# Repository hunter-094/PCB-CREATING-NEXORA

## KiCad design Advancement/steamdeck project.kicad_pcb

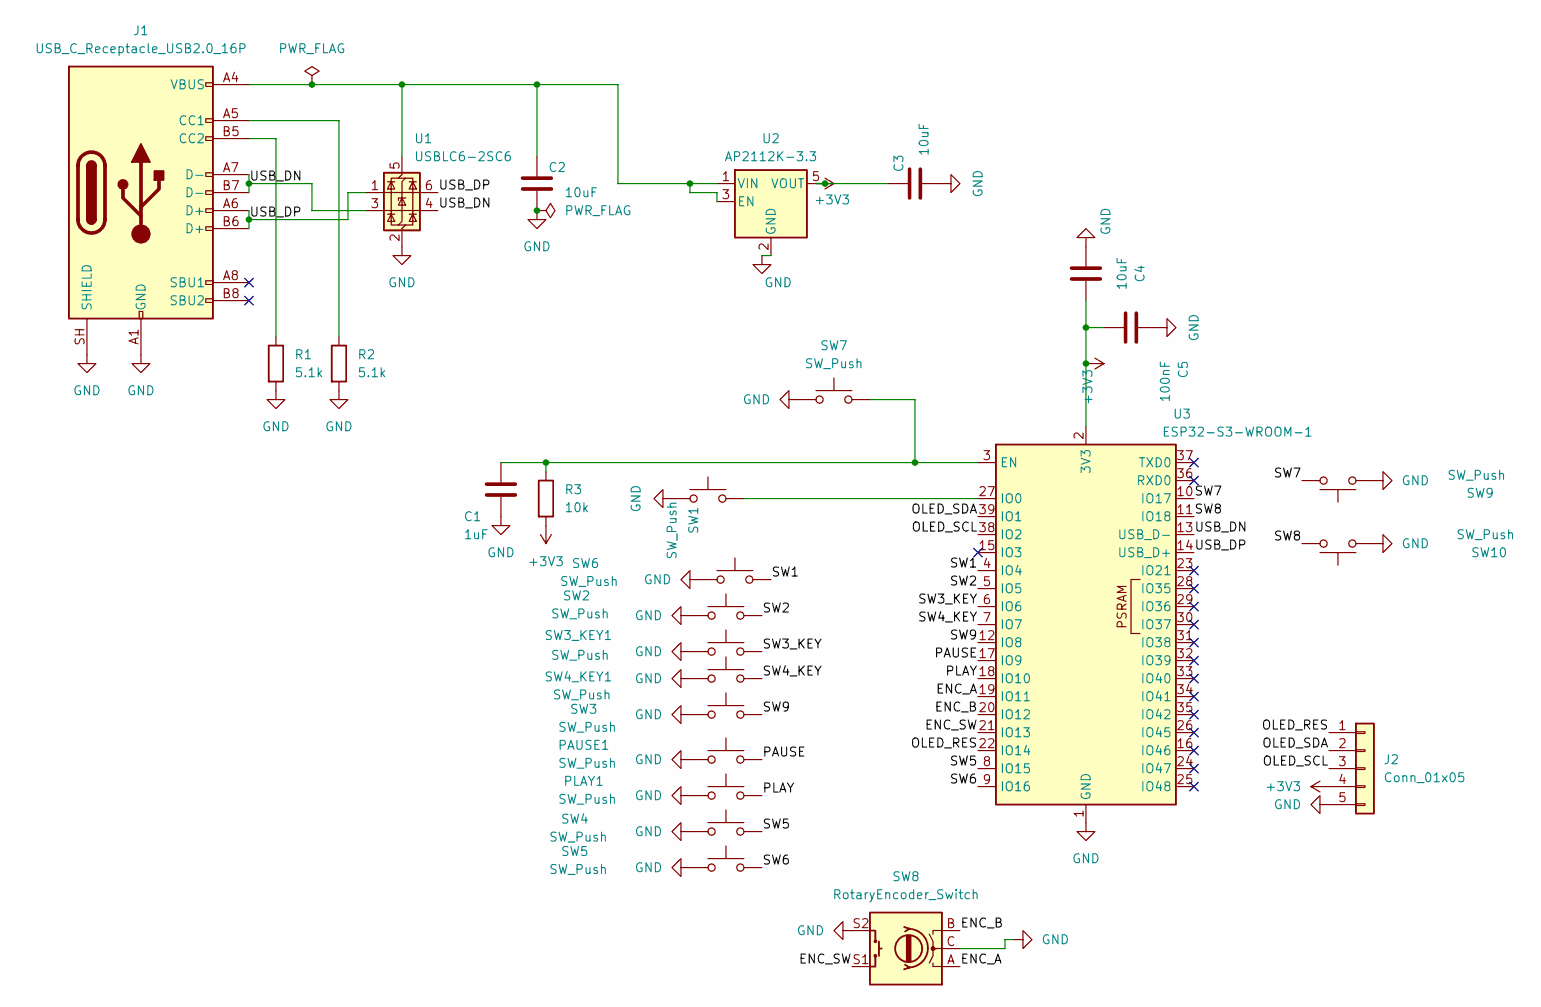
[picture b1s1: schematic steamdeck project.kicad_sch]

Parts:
C1: 1uF; C_0603_1608Metric
C2, C3, C4: 10uF; C_0805_2012Metric
C5: 100nF; C_0603_1608Metric
J1: USB_C_Receptacle_USB2.0_16P; USB_C_Receptacle_HRO_TYPE-C-31-M-12
J2: Conn_01x05; PinSocket_1x05_P2.54mm_Vertical
PAUSE1: SW_Push; SW_Cherry_MX_1.00u_PCB
PLAY1: SW_Push; SW_Cherry_MX_1.00u_PCB
R1, R2: 5.1k; R_0603_1608Metric
R3: 10k; R_0603_1608Metric
SW1, SW7: SW_Push; SW_SPST_PTS645Sx43SMTR92
SW2, SW3, SW3_KEY1, SW4, SW4_KEY1, SW5, SW6, SW9, SW10: SW_Push; SW_Cherry_MX_1.00u_PCB
SW8: RotaryEncoder_Switch; RotaryEncoder_Alps_EC11E-Switch_Vertical_H20mm
U1: USBLC6-2SC6; SOT-23-6
U2: AP2112K-3.3; SOT-23-5
U3: ESP32-S3-WROOM-1

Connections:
+3V3: C3.1, C4.2, C5.1, J2.4, R3.2, U2.5 (VOUT), U3.2 (3V3)
/ENC_A: SW8.A, U3.19 (IO11)
/ENC_B: SW8.B, U3.20 (IO12)
/ENC_SW: SW8.S1, U3.21 (IO13)
/OLED_RES: J2.1, U3.22 (IO14)
/OLED_SCL: J2.3, U3.38 (IO2)
/OLED_SDA: J2.2, U3.39 (IO1)
/PAUSE: PAUSE1.2, U3.17 (IO9)
/PLAY: PLAY1.2, U3.18 (IO10)
/SW1: SW6.2, U3.4 (IO4)
/SW2: SW2.2, U3.5 (IO5)
/SW3_KEY: SW3_KEY1.2, U3.6 (IO6)
/SW4_KEY: SW4_KEY1.2, U3.7 (IO7)
/SW5: SW4.2, U3.8 (IO15)
/SW6: SW5.2, U3.9 (IO16)
/SW7: SW9.2, U3.10 (IO17)
/SW8: SW10.2, U3.11 (IO18)
/SW9: SW3.2, U3.12 (IO8)
/USB_DN: J1.A7 (D-), J1.B7 (D-), U1.3 (I/O2), U1.4 (I/O2), U3.13 (USB_D-)
/USB_DP: J1.A6 (D+), J1.B6 (D+), U1.1 (I/O1), U1.6 (I/O1), U3.14 (USB_D+)
GND: C1.2, C2.2, C3.2, C4.1, C5.2, J1.A1 (GND), J1.A12 (GND), J1.B1 (GND), J1.B12 (GND), J1.SH (SHIELD), J2.5, PAUSE1.1, PLAY1.1, R1.2, R2.2, SW1.1, SW2.1, SW3.1, SW3_KEY1.1, SW4.1, SW4_KEY1.1, SW5.1, SW6.1, SW7.1, SW8.C, SW8.S2, SW9.1, SW10.1, U1.2 (GND), U2.2 (GND), U3.1 (GND), U3.40 (GND), U3.41 (GND)
unnamed: J1.A5 (CC1), R2.1
unnamed: J1.B5 (CC2), R1.1
unnamed: C2.1, J1.A4 (VBUS), J1.A9 (VBUS), J1.B4 (VBUS), J1.B9 (VBUS), U1.5 (VBUS), U2.1 (VIN), U2.3 (EN)
unnamed: C1.1, R3.1, SW7.2, U3.3 (EN)
unnamed: SW1.2, U3.27 (IO0)

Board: 2 copper layers, 27 parts (0 on the bottom side), 26 nets, no tracks yet.

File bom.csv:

Référence,Valeur,Quantité,Empreinte,Description,Lien
U3,ESP32-S3-WROOM-1-N16R8,1,RF_Module:ESP32-S3-WROOM-1,"Module ESP32-S3, 16 Mo flash, 8 Mo PSRAM (PCB final)",https://www.mouser.fr/c/?q=ESP32-S3-WROOM-1-N16R8
U2,AP2112K-3.3,1,Package_TO_SOT_SMD:SOT-23-5,"Régulateur 3,3 V",https://www.lcsc.com/search?q=AP2112K-3.3
U1,USBLC6-2SC6,1,Package_TO_SOT_SMD:SOT-23-6,Protection ESD USB,https://www.lcsc.com/search?q=USBLC6-2SC6
J1,USB-C 16 broches,1,Connector_USB:USB_C_Receptacle_HRO_TYPE-C-31-M-12,Connecteur USB-C CMS,https://www.lcsc.com/search?q=USB-C+16pin
J2,Header femelle 1x05,1,Connector_PinSocket_2.54mm:PinSocket_1x05_P2.54mm_Vertical,Connecteur de l'écran OLED,https://www.amazon.fr/s?k=barrette+femelle+2.54mm
"R1, R2","5,1 kΩ",2,Resistor_SMD:R_0603_1608Metric,Résistances CC de l'USB-C,https://www.lcsc.com/search?q=5.1k+0603
R3,10 kΩ,1,Resistor_SMD:R_0603_1608Metric,Pull-up du reset (EN),https://www.lcsc.com/search?q=10k+0603
C1,1 µF,1,Capacitor_SMD:C_0603_1608Metric,Condensateur du reset,https://www.lcsc.com/search?q=1uF+0603
"C2, C3, C4",10 µF,3,Capacitor_SMD:C_0805_2012Metric,Découplage alimentation,https://www.lcsc.com/search?q=10uF+0805
C5,100 nF,1,Capacitor_SMD:C_0603_1608Metric,Découplage du module,https://www.lcsc.com/search?q=100nF+0603
"SW1, SW7",Bouton tact CMS,2,Button_Switch_SMD:SW_SPST_PTS645Sx43SMTR92,Boutons Boot et Reset,https://www.lcsc.com/search?q=SMD+tact+switch
"SW2-SW6, SW9, SW10, SW3_KEY1, SW4_KEY1, PAUSE1, PLAY1",Switch MX 3 broches,11,Button_Switch_Keyboard:SW_Cherry_MX_1.00u_PCB,9 raccourcis + Pause + Play,https://www.amazon.fr/s?k=switch+cherry+MX+mecanique
SW8,Encodeur EC11 avec bouton,1,Rotary_Encoder:RotaryEncoder_Alps_EC11E-Switch_Vertical_H20mm,Volume et mute,https://www.amazon.fr/s?k=encodeur+rotatif+EC11
-,"Écran OLED 2,42"" SSD1309 128x64 I2C",1,-,"Module écran (5 broches : RES, SDA, SCL, VCC, GND)",https://www.amazon.fr/s?k=ecran+OLED+2.42+pouces+SSD1309+128x64
-,Keycaps MX,11,-,Capuchons des touches,https://www.amazon.fr/s?k=keycaps+MX
-,Knob 15 à 20 mm,1,-,Bouton de l'encodeur,https://www.amazon.fr/s?k=bouton+encodeur+rotatif+15mm
-,Inserts filetés M3,4,-,Fixation dans le boîtier,https://www.amazon.fr/s?k=inserts+filetes+M3+impression+3D
-,Vis M3 6 à 8 mm,4,-,Fixation du PCB,https://www.amazon.fr/s?k=vis+M3+8mm
-,Boîtier impression 3D (PETG ou PLA),1,-,Boîtier 150 x 80 mm,-
-,Câble USB-C avec données,1,-,Alimentation et connexion au PC,-
PROTOTYPE,Carte ESP32-S3-DevKitC-1 N16R8,1,-,Pour tester avant le PCB,https://www.amazon.fr/s?k=ESP32-S3-DevKitC-1+N16R8
PROTOTYPE,Breadboard,1,-,Câblage du prototype,https://www.amazon.fr/s?k=breadboard+830+points
PROTOTYPE,Fils Dupont,1,-,Câblage du prototype,https://www.amazon.fr/s?k=fils+dupont+kit

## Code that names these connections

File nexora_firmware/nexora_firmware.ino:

/*
  NEXORA - firmware ESP32-S3 (WROOM-1 N16R8)
  ------------------------------------------
  - 9 touches de raccourci  -> envoient F13 a F21 (a associer a des actions
    sur le PC avec PowerToys, AutoHotkey, Steam, OBS, etc.)
  - Touches PAUSE / PLAY    -> controle media (lecture/pause, piste suivante)
  - Encodeur rotatif        -> volume +/- ; clic = mute
  - Ecran OLED SSD1309 128x64 (I2C) -> affiche la derniere action et le volume

  Branchement (voir le schema KiCad) :
    Touches : IO4, IO5, IO6, IO7, IO15, IO16, IO17, IO18, IO8
    PAUSE IO9, PLAY IO10
    Encodeur : A IO11, B IO12, bouton IO13
    OLED : SDA IO1, SCL IO2, RES IO14

  Reglages dans l'IDE Arduino (core "esp32" d'Espressif) :
    Carte       : ESP32S3 Dev Module
    USB Mode    : USB-OTG (TinyUSB)
    PSRAM       : OPI PSRAM
    Flash Size  : 16MB
  Bibliotheque a installer : U8g2 (par olikraus)

  Pour flasher : brancher le port USB natif en maintenant le bouton BOOT,
  appuyer sur RESET, puis relacher BOOT.
*/

#include <Arduino.h>
#include <Wire.h>
#include <U8g2lib.h>
#include "USB.h"
#include "USBHIDKeyboard.h"
#include "USBHIDConsumerControl.h"

// ---------- Broches ----------
#define PIN_OLED_SDA 1
#define PIN_OLED_SCL 2
#define PIN_OLED_RES 14

#define PIN_ENC_A  11
#define PIN_ENC_B  12
#define PIN_ENC_SW 13

// ---------- Objets ----------
USBHIDKeyboard        Keyboard;
USBHIDConsumerControl Consumer;
U8G2_SSD1309_128X64_NONAME0_F_HW_I2C u8g2(U8G2_R0, PIN_OLED_RES);

// ---------- Description des touches ----------
enum ActionType { ACT_KEY, ACT_MEDIA };

struct Btn {
  uint8_t       pin;
  const char*   name;     // texte affiche sur l'ecran
  ActionType    type;
  uint16_t      code;     // code HID (clavier) ou code media
  bool          pressed;
  unsigned long lastChange;
};

// Codes HID bruts : F13 = 0x68 ... F21 = 0x70
// Pour changer une action, modifie simplement la ligne correspondante.
Btn buttons[] = {
  {4,  "Touche 1", ACT_KEY,   0x68, false, 0},  // F13
  {5,  "Touche 2", ACT_KEY,   0x69, false, 0},  // F14
  {6,  "Touche 3", ACT_KEY,   0x6A, false, 0},  // F15
  {7,  "Touche 4", ACT_KEY,   0x6B, false, 0},  // F16
  {15, "Touche 5", ACT_KEY,   0x6C, false, 0},  // F17
  {16, "Touche 6", ACT_KEY,   0x6D, false, 0},  // F18
  {17, "Touche 7", ACT_KEY,   0x6E, false, 0},  // F19
  {18, "Touche 8", ACT_KEY,   0x6F, false, 0},  // F20
  {8,  "Touche 9", ACT_KEY,   0x70, false, 0},  // F21
  {9,  "Lecture/Pause", ACT_MEDIA, CONSUMER_CONTROL_PLAY_PAUSE, false, 0},
  {10, "Piste suivante", ACT_MEDIA, CONSUMER_CONTROL_SCAN_NEXT,  false, 0},
};
const uint8_t NB_BTN = sizeof(buttons) / sizeof(buttons[0]);
const unsigned long DEBOUNCE_MS = 20;

// ---------- Encodeur ----------
volatile int16_t encAcc = 0;
volatile uint8_t encState = 0;

void IRAM_ATTR encISR() {
  static const int8_t table[16] = {0, -1, 1, 0, 1, 0, 0, -1, -1, 0, 0, 1, 0, 1, -1, 0};
  encState = ((encState << 2) | (digitalRead(PIN_ENC_A) << 1) | digitalRead(PIN_ENC_B)) & 0x0F;
  encAcc += table[encState];
}

bool encPressed = false;
unsigned long encLastChange = 0;

// ---------- Affichage ----------
String lastAction = "NEXORA pret";
int    volumeLevel = 50;          // estimation locale, juste pour l'affichage
bool   muted = false;
bool   dirty = true;
unsigned long lastDraw = 0;

void draw() {
  u8g2.clearBuffer();
  u8g2.setFont(u8g2_font_helvB10_tr);
  u8g2.drawStr(0, 12, "NEXORA");
  u8g2.drawHLine(0, 16, 128);

  u8g2.setFont(u8g2_font_helvR10_tr);
  u8g2.drawStr(0, 36, lastAction.c_str());

  // Barre de volume
  u8g2.drawFrame(0, 48, 100, 12);
  if (!muted) u8g2.drawBox(2, 50, map(volumeLevel, 0, 100, 0, 96), 8);
  u8g2.setFont(u8g2_font_6x10_tr);
  u8g2.drawStr(104, 58, muted ? "MUT" : String(volumeLevel).c_str());
  u8g2.sendBuffer();
}

void showAction(const String& text) {
  lastAction = text;
  dirty = true;
}

// ---------- Setup ----------
void setup() {
  for (uint8_t i = 0; i < NB_BTN; i++) pinMode(buttons[i].pin, INPUT_PULLUP);
  pinMode(PIN_ENC_A, INPUT_PULLUP);
  pinMode(PIN_ENC_B, INPUT_PULLUP);
  pinMode(PIN_ENC_SW, INPUT_PULLUP);

  attachInterrupt(digitalPinToInterrupt(PIN_ENC_A), encISR, CHANGE);
  attachInterrupt(digitalPinToInterrupt(PIN_ENC_B), encISR, CHANGE);

  Wire.begin(PIN_OLED_SDA, PIN_OLED_SCL);
  u8g2.begin();
  u8g2.setBusClock(400000);

  Keyboard.begin();
  Consumer.begin();
  USB.begin();

  draw();
}

// ---------- Boucle principale ----------
void loop() {
  unsigned long now = millis();

  // 1) Touches (anti-rebond)
  for (uint8_t i = 0; i < NB_BTN; i++) {
    bool down = (digitalRead(buttons[i].pin) == LOW);
    if (down != buttons[i].pressed && now - buttons[i].lastChange > DEBOUNCE_MS) {
      buttons[i].pressed = down;
      buttons[i].lastChange = now;

      if (buttons[i].type == ACT_KEY) {
        if (down) Keyboard.pressRaw(buttons[i].code);
        else      Keyboard.releaseRaw(buttons[i].code);
      } else {
        if (down) Consumer.press(buttons[i].code);
        else      Consumer.release();
      }
      if (down) showAction(buttons[i].name);
    }
  }

  // 2) Encodeur : 4 transitions = 1 cran
  int16_t acc;
  noInterrupts();
  acc = encAcc;
  if (abs(acc) >= 4) encAcc = 0;
  interrupts();

  if (abs(acc) >= 4) {
    if (acc > 0) {
      Consumer.press(CONSUMER_CONTROL_VOLUME_INCREMENT);
      volumeLevel = min(100, volumeLevel + 2);
    } else {
      Consumer.press(CONSUMER_CONTROL_VOLUME_DECREMENT);
      volumeLevel = max(0, volumeLevel - 2);
    }
    Consumer.release();
    muted = false;
    showAction("Volume");
  }

  // 3) Bouton de l'encodeur : mute
  bool encDown = (digitalRead(PIN_ENC_SW) == LOW);
  if (encDown != encPressed && now - encLastChange > DEBOUNCE_MS) {
    encPressed = encDown;
    encLastChange = now;
    if (encDown) {
      Consumer.press(CONSUMER_CONTROL_MUTE);
      Consumer.release();
      muted = !muted;
      showAction(muted ? "Muet" : "Son actif");
    }
  }

  // 4) Rafraichissement de l'ecran (au plus toutes les 50 ms)
  if (dirty && now - lastDraw > 50) {
    draw();
    dirty = false;
    lastDraw = now;
  }
}
